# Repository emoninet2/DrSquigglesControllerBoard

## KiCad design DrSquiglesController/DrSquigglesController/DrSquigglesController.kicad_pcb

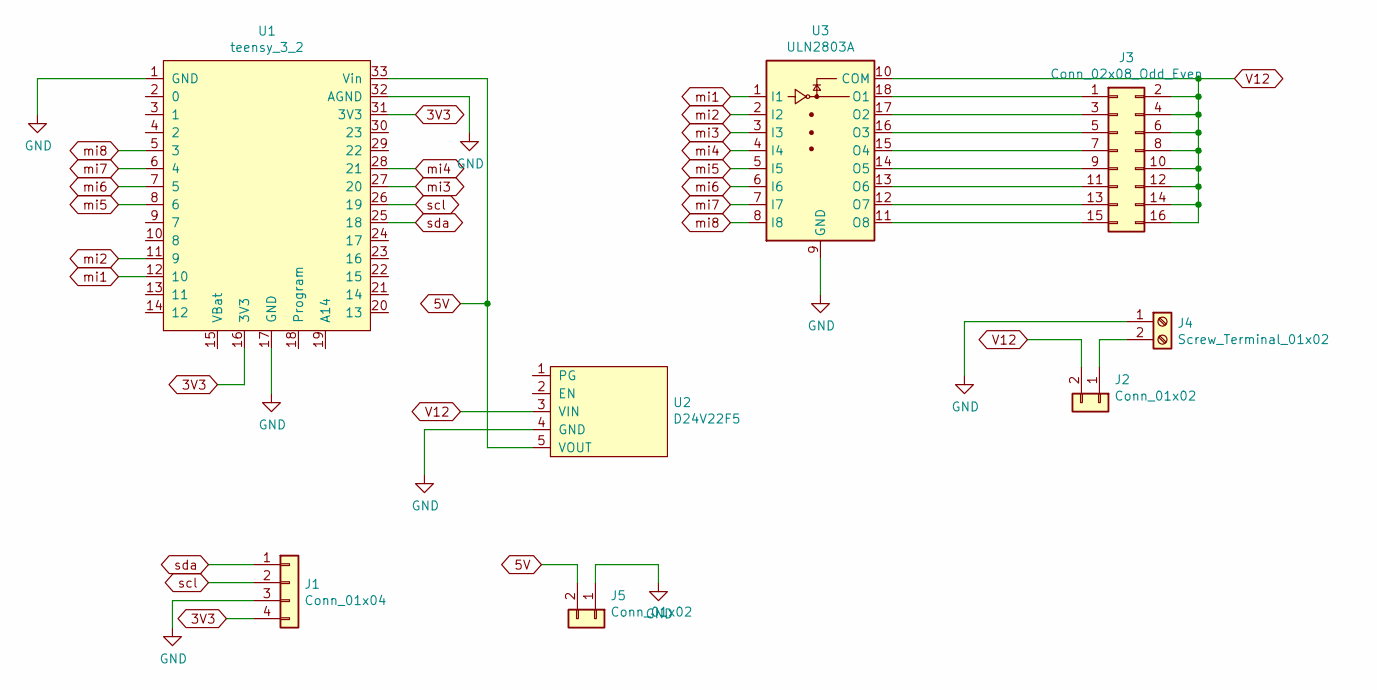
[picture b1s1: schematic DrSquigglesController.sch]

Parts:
J1: Conn_01x04; PinHeader_1x04_P2.54mm_Vertical
J2, J5: Conn_01x02; PinHeader_1x02_P2.54mm_Vertical
J3: Conn_02x08_Odd_Even; PinHeader_2x08_P2.54mm_Vertical
J4: Screw_Terminal_01x02; TerminalBlock_Phoenix_MKDS-1,5-2-5.08_1x02_P5.08mm_Horizont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
U1: teensy_3_2; Teensy_3_2
U2: D24V22F5
U3: ULN2803A; DIP-18_W7.62mm

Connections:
3V3: J1.4, U1.16 (3V3), U1.31 (3V3)
5V: J5.2, U1.33 (Vin), U2.5 (VOUT)
GND: J1.3, J4.1, J5.1, U1.1 (GND), U1.17 (GND), U1.32 (AGND), U2.4 (GND), U3.9 (GND)
unnamed: J2.1, J4.2
unnamed: J3.1, U3.18 (O1)
unnamed: J3.3, U3.17 (O2)
unnamed: J3.5, U3.16 (O3)
unnamed: J3.7, U3.15 (O4)
unnamed: J3.9, U3.14 (O5)
unnamed: J3.11, U3.13 (O6)
unnamed: J3.13, U3.12 (O7)
unnamed: J3.15, U3.11 (O8)
V12: J2.2, J3.2, J3.4, J3.6, J3.8, J3.10, J3.12, J3.14, J3.16, U2.3 (VIN), U3.10 (COM)
mi1: U1.12 (10), U3.1 (I1)
mi2: U1.11 (9), U3.2 (I2)
mi3: U1.27 (20), U3.3 (I3)
mi4: U1.28 (21), U3.4 (I4)
mi5: U1.8 (6), U3.5 (I5)
mi6: U1.7 (5), U3.6 (I6)
mi7: U1.6 (4), U3.7 (I7)
mi8: U1.5 (3), U3.8 (I8)
scl: J1.2, U1.26 (19)
sda: J1.1, U1.25 (18)

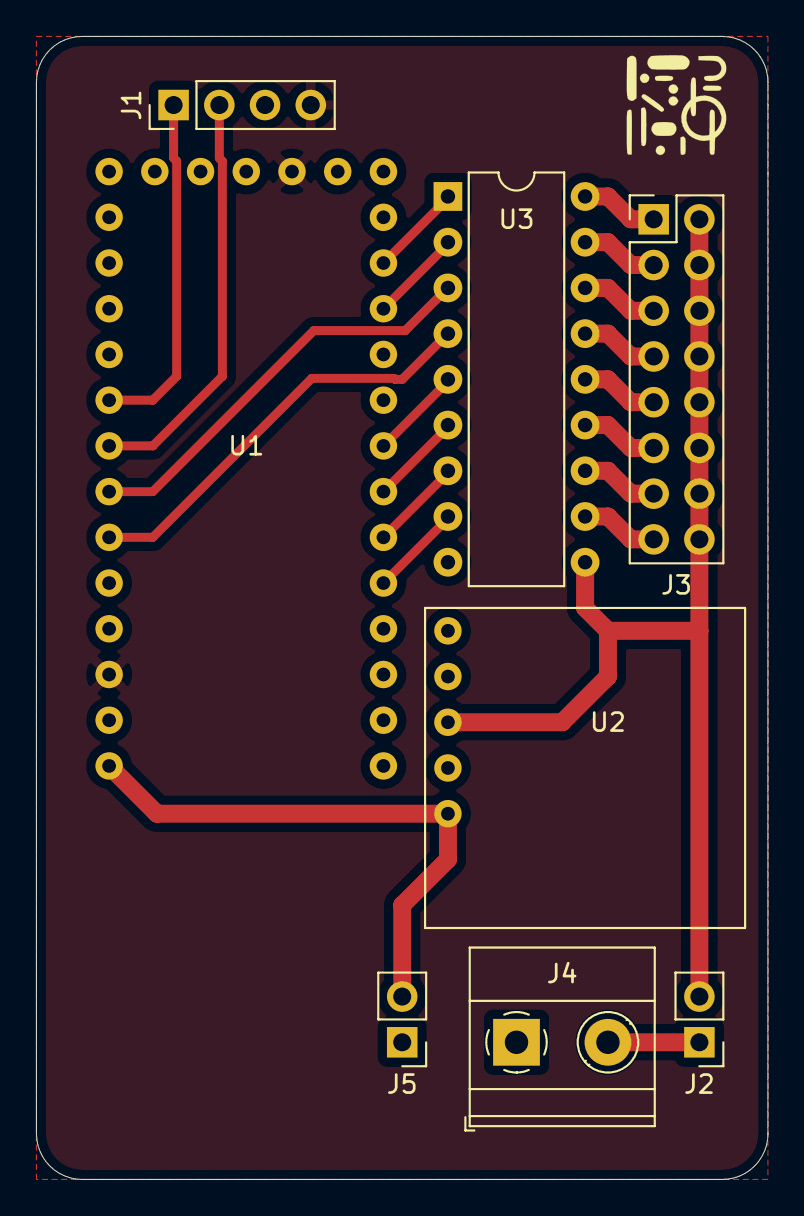
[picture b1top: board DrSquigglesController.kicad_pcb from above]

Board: 2 copper layers, 40.6 x 63.5 mm, 8 parts (0 on the bottom side), 23 nets.

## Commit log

2020-04-05 added existing project
2020-04-05 replaced screw terminal to make space for conecting teensy3.2 USB
2020-04-07 added jumper for raspi power
2020-04-07 added RITMO logo again
2020-04-19 added PCB board image to README.md
